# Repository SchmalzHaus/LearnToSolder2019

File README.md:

# LearnToSolder2019
Glen Lake Elementary Learn To Solder kit for 2019

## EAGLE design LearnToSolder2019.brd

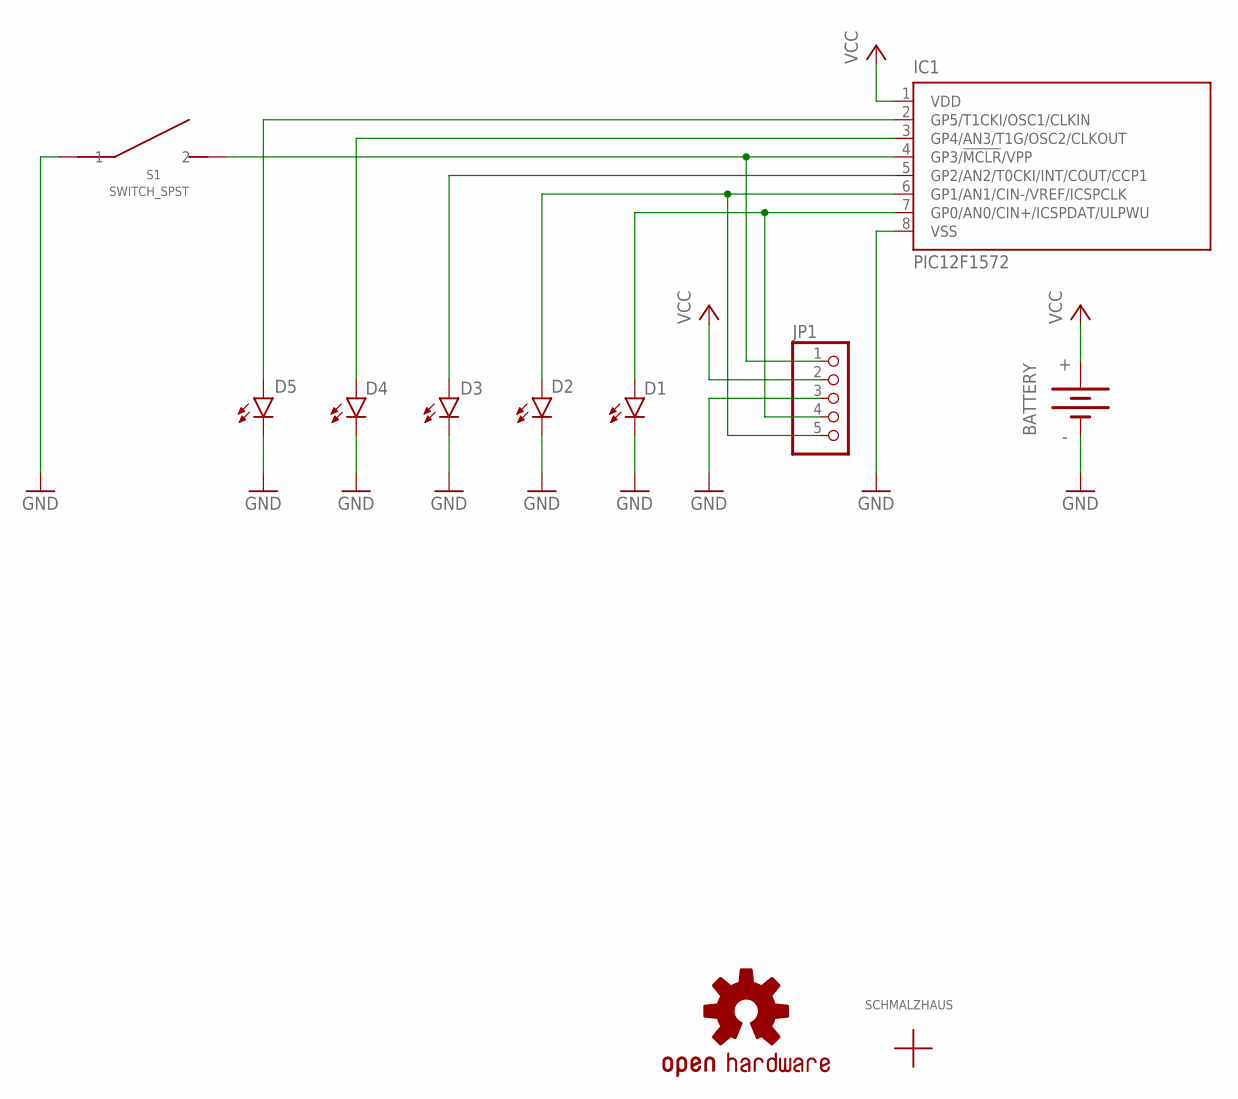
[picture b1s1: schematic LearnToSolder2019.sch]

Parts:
BATTERY: BATTERY20PTH; BATTCOM_20MM_PTH
D1, D2, D3, D4, D5: LED5MM
IC1: PIC12F1572; SO-08
JP1: PINHD-1X5; 1X05
LOGO1: OSHW-LOGOMINI; OSHW-LOGO-MINI
S1: SWITCH_SPST; OMRON-12MMX12MM_SPST-B3F-4000
U$3: SCHMALZHAUSSCHMALZHAUS_SMALL; SCHMALZHAUS_SMALL

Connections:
GND: BATTERY.2 (-), D1.C, D2.C, D3.C, D4.C, D5.C, IC1.8 (VSS), JP1.3, S1.1, S1.2 (1)
unnamed: IC1.4 (GP3/!MCLR!/VPP), JP1.1, S1.3 (2), S1.4 (2)
unnamed: D4.A, IC1.3 (GP4/AN3/T1G/OSC2/CLKOUT)
unnamed: D3.A, IC1.5 (GP2/AN2/T0CKI/INT/COUT/CCP1)
unnamed: D1.A, IC1.7 (GP0/AN0/CIN+/ICSPDAT/ULPWU), JP1.4
unnamed: D2.A, IC1.6 (GP1/AN1/CIN-/VREF/ICSPCLK), JP1.5
unnamed: D5.A, IC1.2 (GP5/T1CKI/OSC1/CLKIN)
VCC: BATTERY.1 (+), IC1.1 (VDD), JP1.2

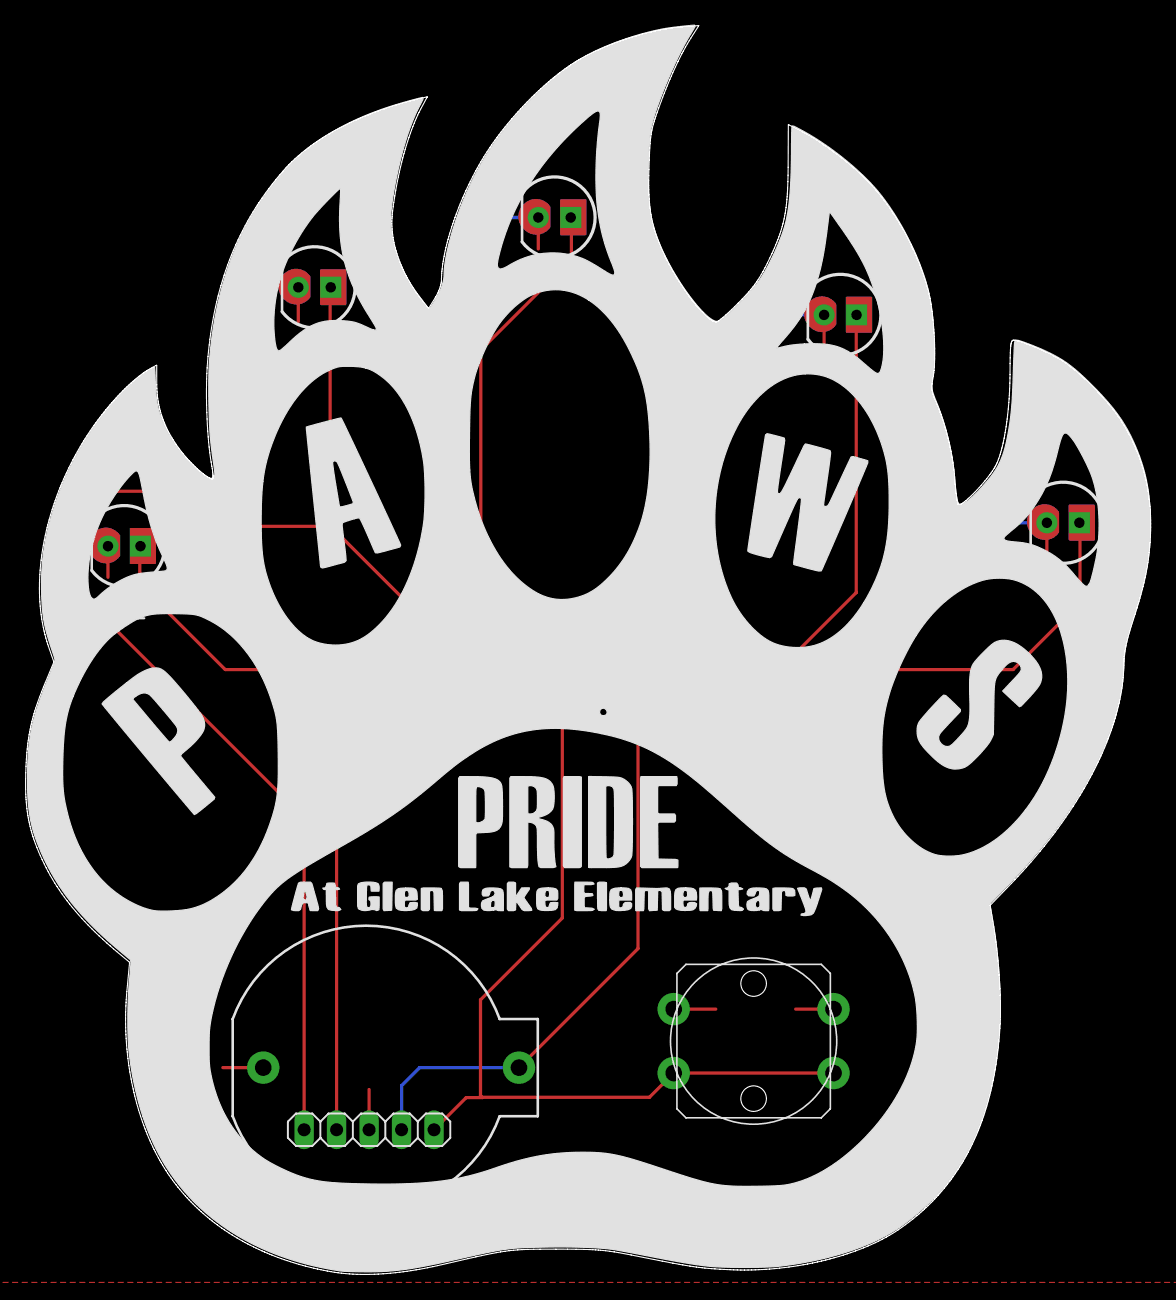
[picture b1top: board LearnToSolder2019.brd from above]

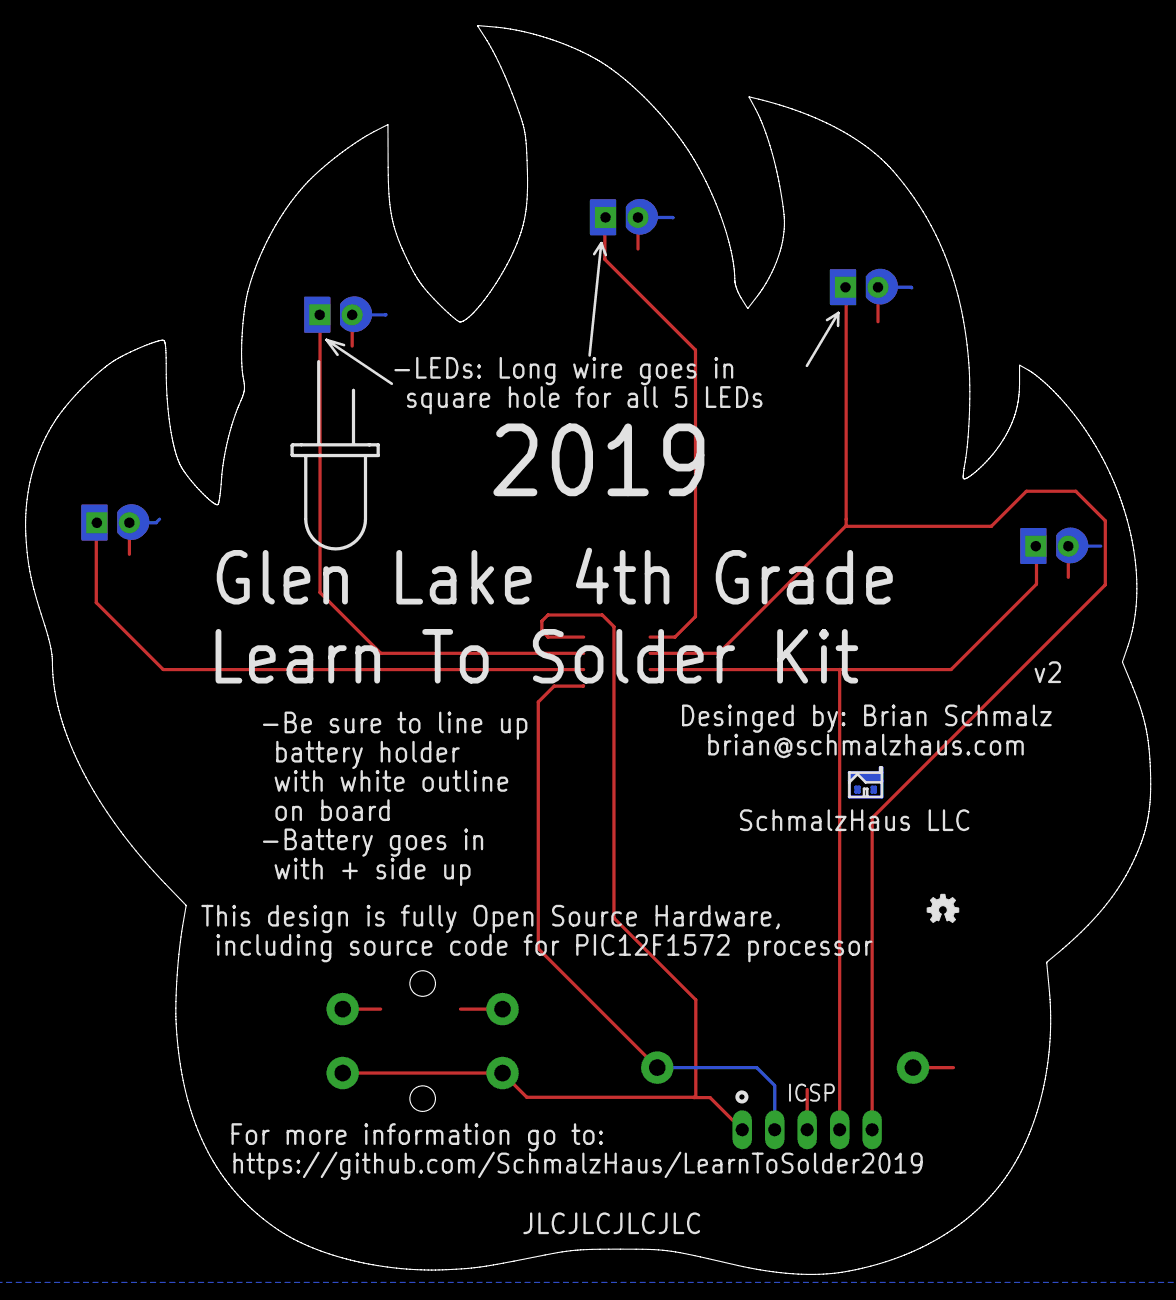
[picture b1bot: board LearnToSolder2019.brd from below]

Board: 2 copper layers, 88.0 x 97.7 mm, 11 parts (2 on the bottom side), 8 nets.

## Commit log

2019-04-02 First check in of LTS2019 - no outline or code work done yet, readme needs to be updated.
2019-04-07 First version (v1) done and set to JLC for test fab
2019-04-13 First test code version working, updated notes from first build.
2019-04-21 Updated silk screen SVG art to include PAWS Pride text and pin 1 indicator for CPU.
2019-04-21 v2 of the board done and sent to JLC for quick test fab, in blue
2019-05-11 WIP: Starting to get stuff in place for this project.
2019-05-14 WIP - getting code set up for non-blocking patterns
2019-05-14 Basic non-blocking pattern code now working. Next step is PWM dimming.
2019-05-16 Fixed a large number of bugs. Implemented pattern array system, PWM working, simple 'wave' pattern now works.
2019-05-17 Final pattern finished.
2019-05-18 Added things to change for 2020 in notes.txt. Readme needs to to be updated properly.

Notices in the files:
parts and their libraries:
SparkFun-Aesthetics: Licensing: Creative Commons ShareAlike 4.0 International - https://creativecommons.org/licenses/by-sa/4.0
